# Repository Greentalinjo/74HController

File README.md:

# 74HC-ontroller

**A game controller built entirely from discrete 74HC logic.** Eight keys, a
diode ROM for a character table, and a real 8-N-1 serial frame out of an RJ45
console port — no microcontroller, no FPGA, no firmware, nothing programmable
anywhere on the board.

## Preface

This project started as an idea for a novel, old-school game controller to
plug into a MikroTik RB4011 that I own and am turning into a gaming console.
The RB4011 already has what a console needs to hear a controller — a serial
console port on an RJ45 jack — so the controller only has to do one thing:
turn a button press into a character on that line.

The twist is *how*. Instead of a microcontroller running a few lines of code,
every step — watching the buttons, noticing a change, looking up the
character, and shifting it out bit by bit at 115200 baud — is done by
sixteen logic chips from the 74HC family, the kind you would find in a 1980s
computer, plus one RS-232 line driver. Change the character a button sends by
moving a diode.

| At a glance | |
|---|---|
| Keys | 5-way navigation cluster + 3 Cherry MX switches |
| Output | 8-N-1 serial, 115200 baud by default, as RS-232 on an RJ45 (Cisco console pinout) or 3.3 V TTL on a header |
| Logic | 16 × 74HC-series ICs + a MAX3232 RS-232 transceiver |
| Key map | an 8 × 7 diode ROM — 56 positions, a diode wherever a bit is 1 |
| Power | one AA cell, boosted to 3.3 V; ~1.3 mA, roughly four weeks of continuous use |
| Board | 150 × 60 mm, 6 layers, 1.6 mm |
| Case | 3D-printed, three colours, sliding battery door |

---

## Contents

1. [How it works — the big picture](#1-how-it-works--the-big-picture)
2. [The pipeline, stage by stage](#2-the-pipeline-stage-by-stage)
3. [Putting it together: the life of a key press](#3-putting-it-together-the-life-of-a-key-press)
4. [What you can configure](#4-what-you-can-configure)
5. [Using it with a MikroTik console](#5-using-it-with-a-mikrotik-console)
6. [The hardware](#6-the-hardware)
7. [The case](#7-the-case)
8. [Building one](#8-building-one)
9. [Repository layout](#9-repository-layout)

---

## 1. How it works — the big picture

A microcontroller would handle a key press with a loop and an interrupt. This
board does the same job as a small **pipeline of hardware stages**, each on
its own schematic sheet, each handing a signal to the next:

```mermaid
flowchart LR
    subgraph clock["Power, clock, reset"]
        P["AA cell → boost → 3.3 V"]
        C["crystal → 74HC4060 → baud tap<br/>CLK / nCLK"]
        R["power-on reset<br/>POR_n"]
    end

    K["8 keys<br/>RC + Schmitt debounce"] --> L["74HC151<br/>LIVE key"]
    S["74HC161<br/>scan counter"] -- "address" --> L
    S -- "address" --> M["74HC259<br/>state memory"]
    M --> T["74HC151<br/>STORED key"]
    S -- "address" --> T
    L --> X["74HC86<br/>DIFF = LIVE xor STORED"]
    T --> X
    X --> B["74HC74<br/>BUSY"]
    B -- "freeze" --> S
    B --> Q["74HC161 + 74HC138<br/>frame sequencer"]
    Q -- "state 10: store" --> M
    S -- "address" --> D["74HC238 + diode ROM<br/>the character"]
    D --> SR["2 × 74HC165<br/>shift register"]
    SR --> G["74HC32<br/>output gate"]
    G --> O["JP4: TTL header<br/>or MAX3232 → RJ45"]
```

The idea in one paragraph: a counter **scans** the eight keys one at a time,
comparing each key's **live** state with the state the board **remembers**.
When they differ, a key has changed. The board then **freezes the scan** on
that key, uses the key's number to select a row of the **diode ROM** — which
presents that key's character — **shifts** the character out as a serial
frame, **stores** the key's new state so the difference disappears, and
**resumes** scanning. Everything is clocked by the baud-rate clock, so the
whole machine runs in lock-step with the serial line.

---

## 2. The pipeline, stage by stage

The schematic is split into seven sheets, in the order a signal travels
through them. A PDF of the whole schematic is in
[`docs/schematic.pdf`](docs/schematic.pdf).

### Stage 1 — Power, clock and reset *(sheet: Power, Clock, Reset)*

Everything else depends on three things from this sheet.

**Power.** One AA cell goes through the power switch (SW10) into an
**ME2108A33 boost converter** (U18, with L1, D3 and C1), which makes the
board's single **3.3 V** rail. It starts from a 0.9 V cell and keeps
regulating down to 0.45 V, so the battery is used to the end. JP1 can instead
take power from the TTL header. D1 is the power LED.

**Clock.** A **3.6864 MHz crystal** drives the oscillator inside a
**74HC4060** (U1), which also divides the frequency by powers of two. Jumper
**JP2** picks one of those outputs as the bit clock, `CLK` — by default
3.6864 MHz ÷ 32 = exactly **115200 Hz**, one tick per serial bit. A Schmitt
inverter makes `nCLK`, its opposite edge, which the control logic uses.

**Reset.** An RC network (R6, C5) and two Schmitt inverters hold `POR_n` low
for about 87 ms at switch-on, which clears the state memory, the scanner and
the BUSY flag — so the controller never sends a burst of junk characters when
it powers up. SW9 is a manual reset button.

### Stage 2 — Keys and debounce *(sheet: Keys and Debounce)*

Each of the eight keys has its own complete **debounce cell**: a 10 kΩ
pull-up, a 1 kΩ series resistor, a 1 µF capacitor to ground and a **74HC14
Schmitt-trigger** inverter.

```
+3V3 ──[10k]──┬──[1k]── switch ── GND
              │
             1µF          ──► 74HC14 ──► KEYn  (high while pressed)
              │
             GND
```

The cell is deliberately **asymmetric**: pressing discharges the capacitor
through 1 kΩ (a ~1.7 ms response), releasing recharges it through 10 kΩ
(~7.4 ms). The slow edges swallow contact bounce, and the Schmitt trigger
turns the slow analogue ramp into one clean logic edge.

The keys are **KEY0–KEY4**: the five directions of an SJMS 5-way navigation
cluster (SW1, one package) — **KEY5–KEY7**: three Cherry MX switches (SW6–SW8).

### Stage 3 — Scanner and memory *(sheet: Scanner and Memory)*

This stage decides *whether* anything needs sending.

* A **74HC161 counter** (U4) steps a 3-bit address, `ADDR0–2`, through the
  eight keys, one key per clock tick. A full sweep takes eight bit times.
* A **74HC151 multiplexer** (U5) reads the addressed key's live state: `LIVE`.
* A **74HC259 addressable latch** (U6) is the board's memory — eight bits
  holding the last state that was *reported* for each key.
* A second **74HC151** (U7) reads the remembered state of the same key:
  `STORED`. (The '259 has no read-back port of its own, so this second
  multiplexer is essential.)
* A **74HC86 XOR** gate compares the two: `DIFF = LIVE xor STORED`.

`DIFF` goes high exactly when the key under the scanner has changed since it
was last reported. That is the only event this whole machine reacts to.

### Stage 4 — Transmit sequencer *(sheet: Transmit Sequencer)*

This stage runs a transmission once `DIFF` says there is something to send.

* **`BUSY`** — a 74HC74 flip-flop (U9A) captures `DIFF` on the `nCLK` edge.
  While `BUSY` is high, the scan counter is **frozen** through its count
  enables. The clock itself is never gated, so there are no glitches.
* A second **74HC161** (U10) counts the bit times of the frame, and a
  **74HC138** decoder (U11) picks out two moments from that count:
  * **State 10** — the frame has finished, so it pulses the 74HC259's write
    enable. The key's new state is stored, `DIFF` falls, and on the next edge
    `BUSY` clears itself and the scanner moves on.
  * **State 11** — a lock-up escape. If `DIFF` somehow failed to clear, the
    second flip-flop (U9B) forces `BUSY` off, so the controller can never
    freeze for good.

The whole event takes **11 bit times**: 10 for the frame, 1 to store and
resume. That's about 95 µs at 115200 baud.

### Stage 5 — ASCII diode ROM *(sheet: ASCII Diode ROM)*

This stage decides *what* gets sent. It is a real read-only memory, built
from diodes:

* A **74HC238 decoder** (U14) takes the frozen key address and drives exactly
  one of eight **rows** high — one row per key.
* Seven **columns** run across the rows, one per bit of the ASCII code
  (b0–b6), each held low by a 15 kΩ pull-down (R30–R36).
* Where a bit should be 1, a **diode** connects that key's row to that bit's
  column (anode to the row, cathode to the column). Driving the row pulls
  those columns high; the rest stay low.

Of the 56 positions (8 keys × 7 bits), **27 are fitted** for the default key
map. The decoder is only enabled while `DIFF` is high, so the ROM draws
nothing at rest.

### Stage 6 — UART shift register *(sheet: UART Shift Register)*

Two **74HC165 shift registers** (U15, U16) are chained into a 16-bit
register that holds the whole frame:

| Frame bit | Comes from |
|---|---|
| start (0) | tied to ground |
| b0 … b6 | the ROM columns |
| bit 7 | make/break flag (see §4) |
| stop (1) | tied to 3.3 V |
| idle (1s) | tied to 3.3 V |

While the board is idle, `BUSY` holds the registers in **parallel load**, so
the start bit is already waiting on the output. The instant `BUSY` rises they
start shifting — one bit per `nCLK` — which produces the serial frame
directly, least-significant bit first.

A **74HC32 OR gate** (U13) then forms the final line:
`TX = shift register OR not-BUSY OR SUPPRESS`. `not-BUSY` parks the line high
(idle) between frames, and `SUPPRESS` blanks a key-*release* frame when break
codes are turned off.

### Stage 7 — Output *(sheet: Output Stage)*

The finished 3.3 V serial line goes to **JP4**, which sends it one of two ways:

* **RS-232** — through a **MAX3232** (U17) to the **RJ45** console jack, using
  the Cisco console pinout that MikroTik and most network gear use.
* **3.3 V TTL** — to the 4-pin header **J3**, for a USB-serial adapter or
  another board.

The MAX3232's spare receiver also converts the *other* direction: whatever
the connected device prints on its console comes back as 3.3 V TTL on J3 pin
3, so you can watch the console while the controller drives it.

---

## 3. Putting it together: the life of a key press

Everything is timed in **bit times** (one `CLK` period: 8.7 µs at 115200
baud). The control logic acts on `nCLK`, half a bit away from the scanner's
`CLK`, so the scan address is always settled before anything reads it.

| When | What happens |
|---|---|
| — | You press a key. The debounce cell settles, and `KEYn` goes high about 1.7 ms later. |
| within 8 bit times | The scanner reaches that key. `LIVE` = 1, `STORED` = 0, so **`DIFF` = 1**. |
| f0 | `BUSY` rises on `nCLK`. The scanner **freezes**, the ROM row for this key is driven, and the shift registers start sending — the **start bit** is already on the line. |
| f1 – f7 | ASCII bits **b0 … b6**, straight from the diode ROM. |
| f8 | **bit 7** (0 unless make/break codes are on). |
| f9 | **stop bit**. |
| f10 | Sequencer state 10: the new key state is **written into memory**. `DIFF` falls. |
| f11 | `BUSY` clears itself. The scanner **resumes**. |

Releasing the key is the same event in reverse: the key now differs from
memory again, so another frame is sent, or quietly suppressed if break codes
are off.

Because each change is handled on its own sweep, pressing all eight keys at
once produces eight clean frames back to back (8.8 ms at 9600 baud, under
1 ms at 115200). Nothing is lost and nothing is merged, since only one key
can be transmitting at a time.

---

## 4. What you can configure

Everything is set with jumpers, solder bridges and diodes. There's no
firmware to reflash.

### Jumpers at a glance

| Ref | What it sets | Options | Default |
|---|---|---|---|
| **JP1** | Power source | 1-2 AA cell via the boost converter · 2-3 from TTL header J3 pin 4 | 1-2 |
| **JP2** | Baud rate | one shunt across one of seven columns (below) | column 2 = 115200 |
| **JP3** | Break codes | open = press only · fitted = press *and* release | open |
| **JP4** | Output | 1-2 RS-232 on the RJ45 · 2-3 3.3 V TTL on J3 | 2-3 |
| **JP5** | Both outputs | solder bridge: drive RS-232 *and* TTL at once | open |
| **JP6 / JP7** | RJ45 cable type | both 2-3 straight patch cable · both 1-2 rollover console cable | 2-3 |
| **JP8 / JP9** | Handshake | solder bridges that assert DSR / CTS, for devices that insist | open |

### Baud rate — JP2 and the crystal

JP2 picks a divider tap from the 74HC4060. Its seven columns follow the
chip's pin order, **not** baud order. That keeps the wiring uncrossed, and a
table on sheet 2 of the schematic maps them.

| JP2 column | 1 | 2 | 3 | 4 | 5 | 6 | 7 |
|---|---|---|---|---|---|---|---|
| '4060 tap | Q6 ÷64 | Q5 ÷32 | Q7 ÷128 | Q4 ÷16 | Q10 ÷1024 | Q8 ÷256 | Q9 ÷512 |
| **3.6864 MHz** (fitted) | 57600 | **115200** | 28800 | 230400 | 3600 | 14400 | 7200 |
| 4.9152 MHz | 76800 | 153600 | 38400 | 307200 | 4800 | 19200 | **9600** |

115200 and 9600 differ by a factor of 12, not a power of two, so no single
crystal reaches both. For a 9600-baud controller, fit a 4.9152 MHz crystal
and use column 7.

### The key map — moving diodes

Each key sends the 7-bit ASCII code wired into its row of the ROM. The diode
for **key *k*, bit *b*** is **D2*kb***. For example, D245 is key 4, bit 5.
Fit a diode wherever the bit should be 1.

| Key | Button | Sends | Code | Diodes fitted |
|---|---|---|---|---|
| 0 | nav centre / OK | Enter (CR) | 0x0D | D200 D202 D203 |
| 1 | nav up | Tab | 0x09 | D210 D213 |
| 2 | nav down | Esc | 0x1B | D220 D221 D223 D224 |
| 3 | nav left | Ctrl-C | 0x03 | D230 D231 |
| 4 | nav right | `/` | 0x2F | D240 D241 D242 D243 D245 |
| 5 | MX 1 | `?` | 0x3F | D250 D251 D252 D253 D254 D255 |
| 6 | MX 2 | Space | 0x20 | D265 |
| 7 | MX 3 | `q` | 0x71 | D270 D274 D275 D276 |

The silkscreen labels the grid like a table, since 56 designators would not
fit. Across the top is `D20 21 22 … 27`, one label per key column. Down the
right side is `0`–`6`, one per bit, next to that bit's pull-down R30–R36. A
diode's designator is the label above it followed by the digit beside it.

### Press-only or make/break — JP3

* **Open (default):** a key sends its character when pressed and nothing on
  release. This is plain typing, the right choice for a console.
* **Fitted:** a press sends `0x80 | code` and a release sends `code`. Bit 7
  carries the key's state, which gives a game true key-down/key-up events.

### Output — JP4, JP5, JP6/JP7, JP8/JP9

* **JP4** chooses RS-232 on the RJ45 or 3.3 V TTL on J3. The unused output is
  held at its idle level, not left floating.
* **JP5** drives both outputs at once.
* **JP6/JP7** move the transmit and receive lines between RJ45 pins 3 and 6,
  so both a straight patch cable and a rollover console cable work. Always
  move them together.
* **JP8/JP9** assert DSR and CTS from a spare driver. RouterOS doesn't need
  them.

**J3 (TTL header):** 1 GND · 2 TXD out · 3 RXD (the far end's console, as
3.3 V TTL) · 4 +3.3 V, in or out depending on JP1.

### Other options

* **Power LED:** leave D1 and R3 off to save 0.28 mA, about a quarter of the
  idle current.
* **R53** stays unfitted. It belonged to a 5 V version of the design and
  would now pull the TTL output below a 3.3 V input's threshold.

---

## 5. Using it with a MikroTik console

1. Set **JP4 to 1-2** (RS-232), and leave JP6/JP7 on 2-3.
2. Connect the controller's RJ45 to the router's **Serial** console port with
   an ordinary straight Ethernet patch cable.
3. The console runs at **115200 8-N-1**, which is JP2's default. RouterBOOT's
   console rate can't be changed, which is why the controller runs at
   115200 rather than 9600.
4. Switch on. Every key press arrives on the console as a plain keystroke,
   ready for whatever is reading it.

For a PC instead, set JP4 to 2-3 and plug a 3.3 V USB-serial adapter into
J3.

---

## 6. The hardware

* **150 × 60 mm, 6-layer, 1.6 mm.** Signals run on the outer layers. Ground
  is poured on the top, bottom and three inner layers, and the 3.3 V supply
  has its own inner plane.
* **Front:** the navigation cluster, the three MX switches, the diode ROM and
  its decoder and pull-downs, one of the shift registers and some decoupling.
* **Back:** the rest of the logic, the RJ45, the TTL and jumper headers, the
  power switch, the reset button and the AA holder.
* **Parts:** all logic in SOIC. Passives are 0603/0402, with 0805 for the 1 µF
  debounce capacitors, and the ROM diodes are SOD-523. Through-hole parts are
  used only where needed: switches, connectors, headers, the AA holder, C1
  and D3.
* **Four M3 mounting holes** (H1–H4) take the case screws.

Three parts have requirements the footprint alone doesn't capture:

* **C30–C37 and C5 (1 µF) must be 0805 X7R.** A 1 µF 0402 part loses so much
  capacitance under DC bias that the debounce timing guarantee breaks at
  9600 baud.
* **C3/C4 (30 pF crystal load) must be C0G/NP0**, to keep the oscillator
  stable and starting reliably.
* **U17 must be a MAX3232** (or MAX232A/SP3232), not a plain MAX232, which
  needs 1 µF pump capacitors. The logic must be **74HC**, not 74HCT or 74LS.

### How it was checked

Before any copper was ordered, the design's netlist was run in a purpose-built
logic simulator that models every IC against its datasheet truth table.
Switches were driven through the real RC debounce values, and the serial
output was decoded like a real UART receiver. The runs covered:
* 108 scenarios, including every key, eight keys at once, bounce, make/break,
  both outputs and a deliberate lock-up;
* 1,268 randomised and exhaustive assertions, including all 255 key
  combinations;
* a DC noise-margin check of every logic level at 3.3 V.

The simulator isn't part of this repository. The schematic passes KiCad ERC
with no errors, and the board passes DRC and matches the schematic.

---

## 7. The case

A three-piece 3D-printed enclosure, ready to slice, in [`case/`](case/):

| File | Part | Print |
|---|---|---|
| `top_with_trim.3mf` | top shell, holding the switches | three colours: plate, trim and logo inlays. Print plate side down, no supports |
| `bottom.3mf` | bottom shell | print on its raised hump. Support only the flat undersides (grid supports, build plate only, 2–3 interface layers, a brim) |
| `door.3mf` | battery door | outer face down, no supports |

The case is shaped to be held in both hands from the ends. The bottom steps
down only where the tall parts are (the battery, power switch and RJ45) and
slopes up everywhere else. It has:
* windows over every jumper header;
* a pinhole for the reset button;
* a pocket for the power switch lever;
* a small light hole for the power LED;
* an RJ45 opening in the top wall.

**Hardware:** five **M3 × 8 pan-head screws** and five **M3 heat-set
inserts**, which go in 4.2 mm holes up to 8 mm deep.

**Assembly:**
1. Clip the switches into the top plate and solder the PCB to them.
2. Press heat-set inserts into the tops of the bottom shell's four posts, and
   the fifth into the battery door's screw boss, from underneath.
3. Close the bottom and drive four screws down through the counterbored holes
   in the top, so the heads sit flush, through the PCB and into the inserts.
4. Drop the battery door into its seat, slide it right so its tongues go
   under the lip, and fix it with the fifth screw.

---

## 8. Building one

1. **The PCB.** Open `kicad/logic-macropad.kicad_pro` in **KiCad 10** or newer
   and plot gerbers and drill files. The project is self-contained, with its
   own symbol and footprint libraries. Order 6 layers, 1.6 mm, FR-4. Nothing
   on the board is impedance-sensitive, so any standard stackup works.
2. **The parts.** Every symbol carries its specification and an example part
   number in its fields. *Tools → Generate BOM* in the schematic editor, or
   `kicad-cli sch export bom`, lists them. The 29 unused ROM positions and
   R53 are marked *do not populate*.
3. **Assembly.** Everything is hand-solderable, but the SOD-523 ROM diodes are
   small. Fit only the diodes for your key map (§4). Set the jumpers, fit an
   AA cell, and switch on.

---

## 9. Repository layout

```
kicad/                          the KiCad 10 project
  logic-macropad.kicad_pro        project, design rules
  logic-macropad.kicad_sch        root sheet: block diagram, the seven stages
  01_power_clock.kicad_sch        stage 1  power, clock, reset
  02_keys_debounce.kicad_sch      stage 2  keys and debounce
  03_scanner.kicad_sch            stage 3  scanner and memory
  04_sequencer.kicad_sch          stage 4  transmit sequencer
  05_ascii_rom.kicad_sch          stage 5  ASCII diode ROM
  06_uart_tx.kicad_sch            stage 6  UART shift register
  07_output.kicad_sch             stage 7  output stage
  logic-macropad.kicad_pcb        the 6-layer board
  lib/, logic-macropad.pretty/    project symbols and footprints
case/                           print-ready 3MF files for the enclosure
docs/
  schematic.pdf                   the full schematic
  images/                         renders used in this README
```

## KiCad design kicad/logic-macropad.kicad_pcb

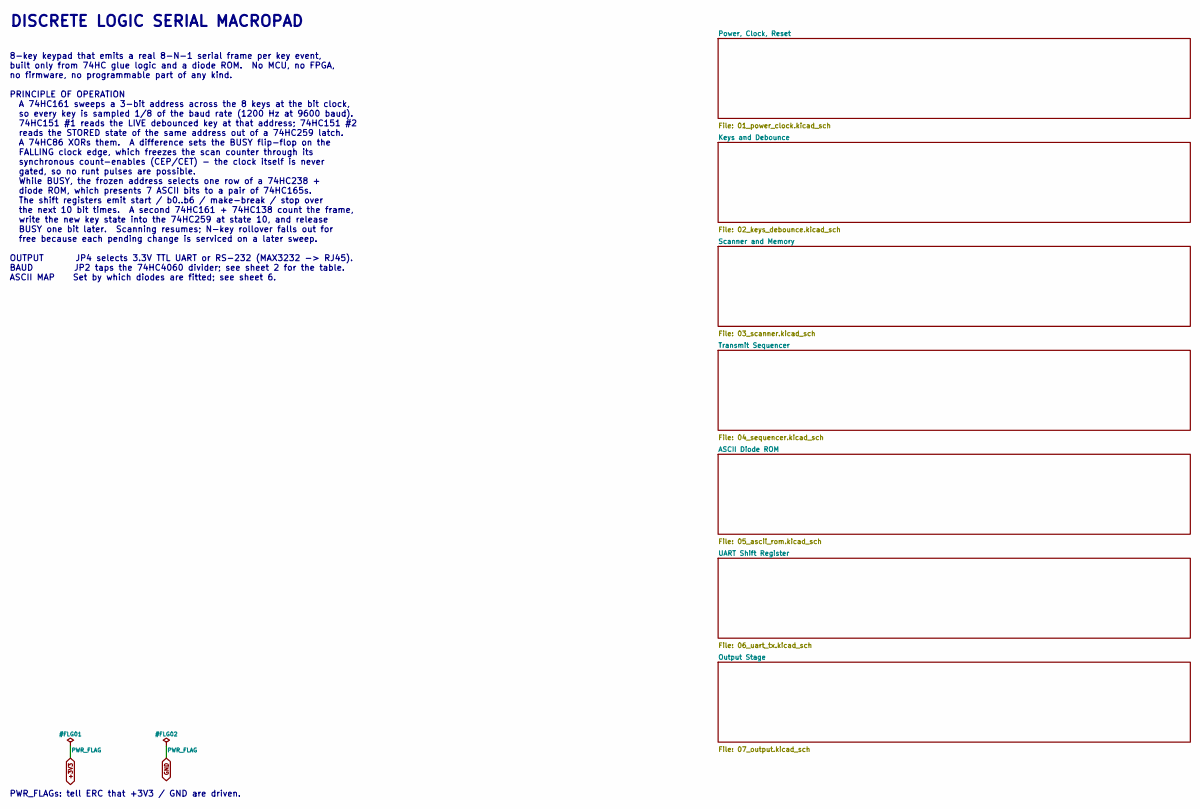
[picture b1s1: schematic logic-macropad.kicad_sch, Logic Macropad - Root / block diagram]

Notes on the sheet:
8-key keypad that emits a real 8-N-1 serial frame per key event, built only from 74HC glue logic and a diode ROM. No MCU, no FPGA, no firmware, no programmable part of any kind. PRINCIPLE OF OPERATION A 74HC161 sweeps a 3-bit address across the 8 keys at the bit clock, so every key is sampled 1/8 o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
PWR_FLAGs: tell ERC that +3V3 / GND are driven.
DISCRETE LOGIC SERIAL MACROPAD

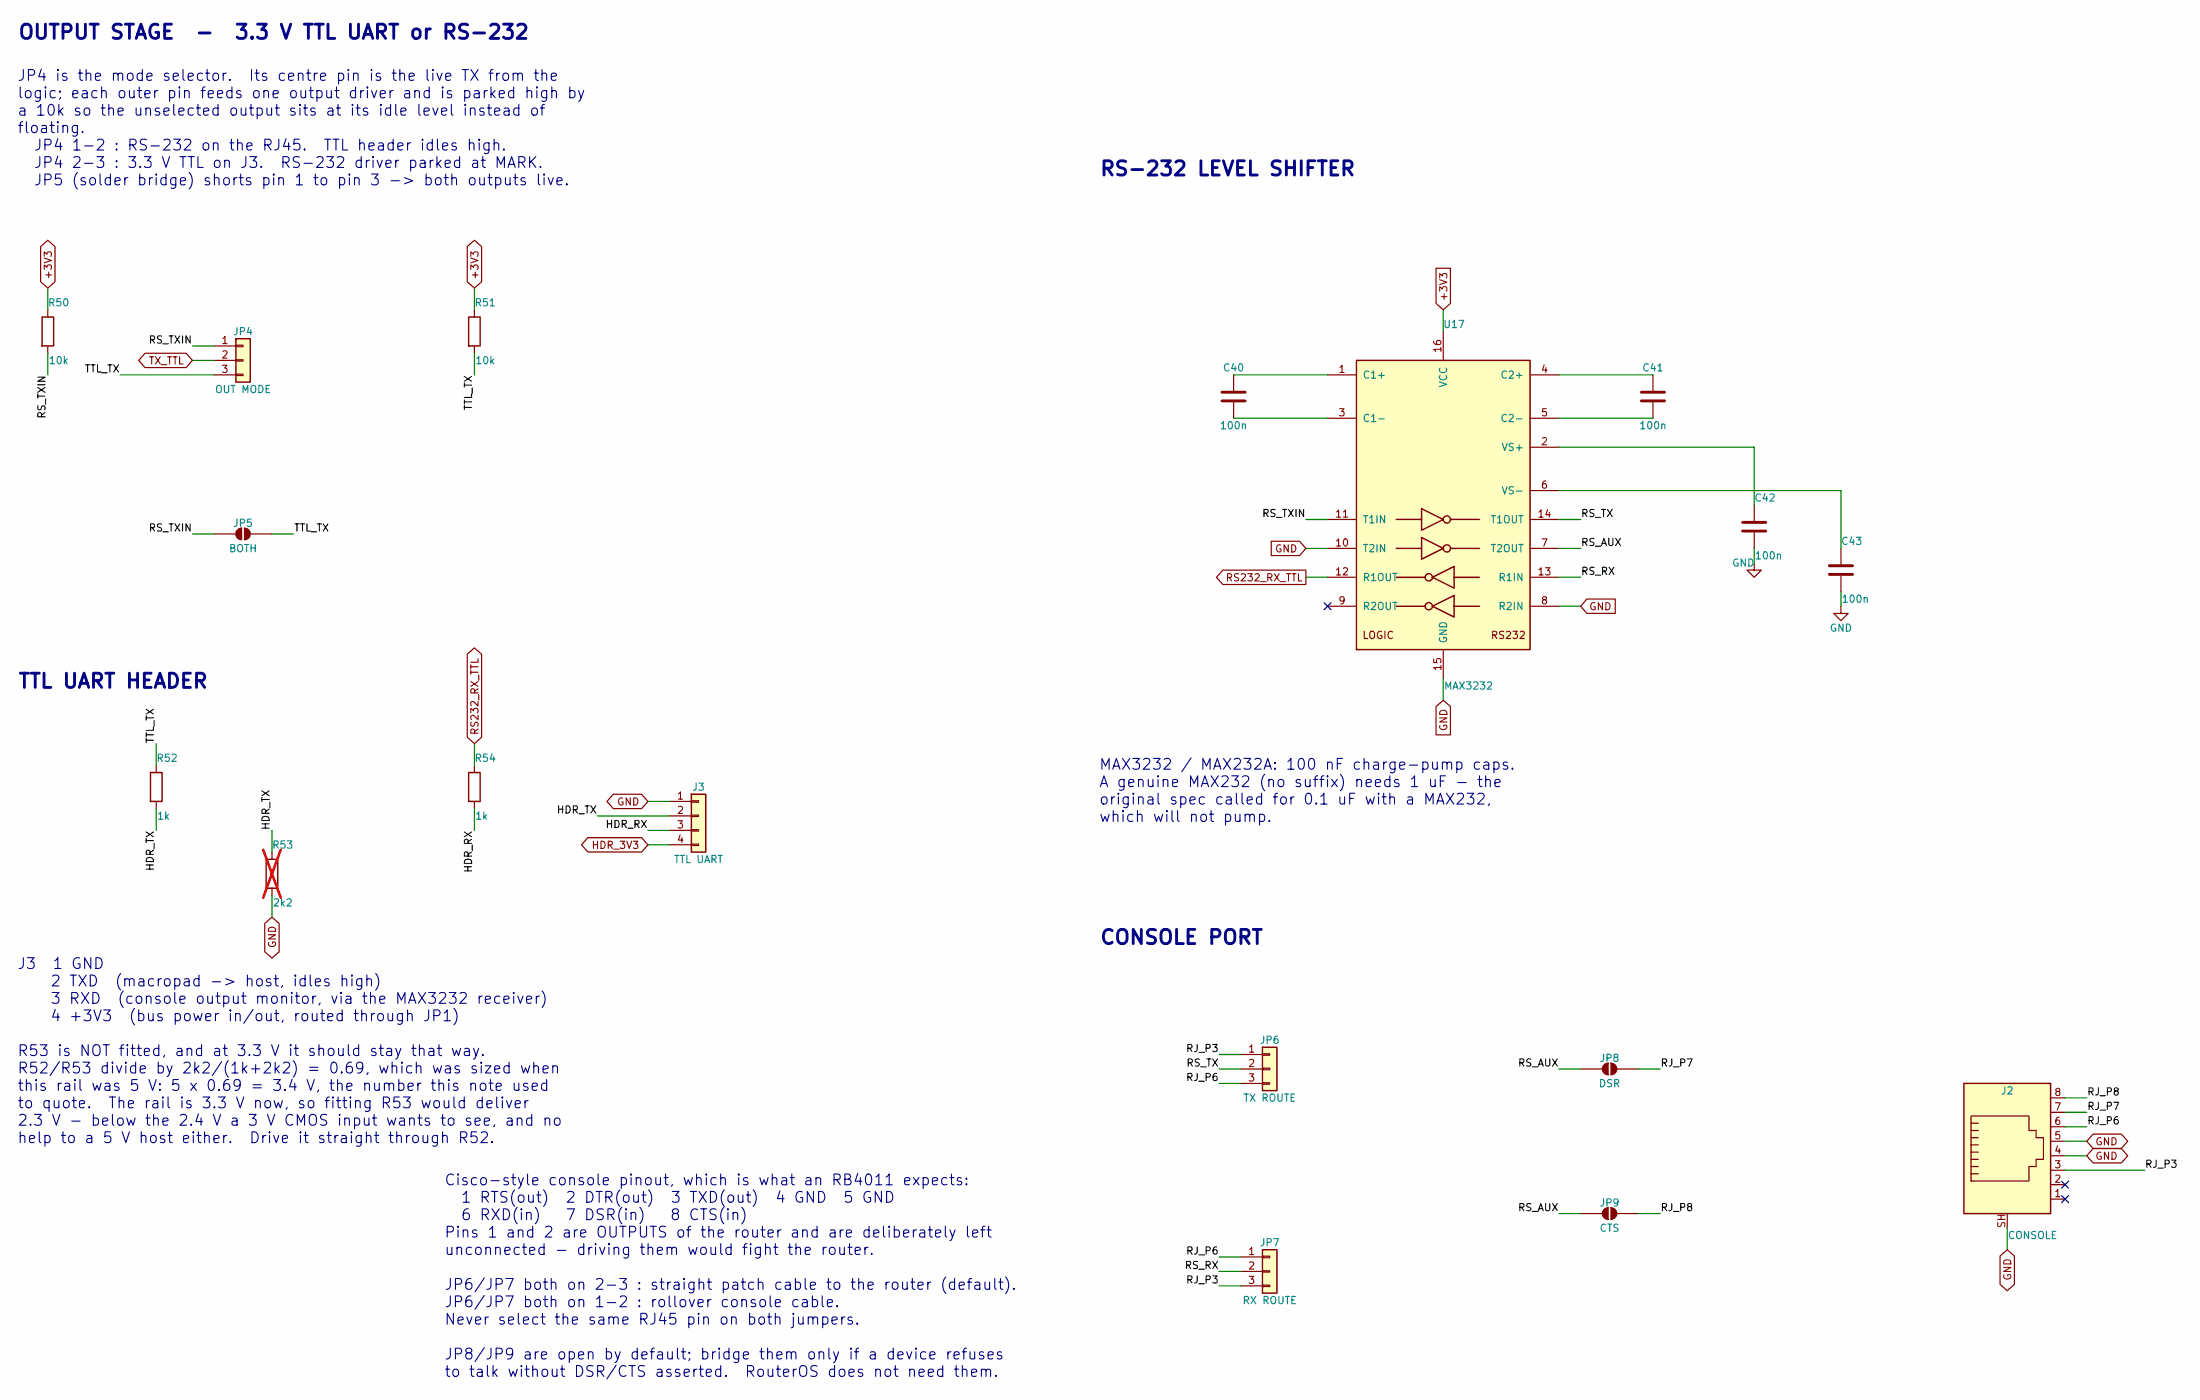
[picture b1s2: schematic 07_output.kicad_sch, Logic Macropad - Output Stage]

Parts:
C40, C41, C42, C43: 100n; C_0402_1005Metric; MPN GRM155R71H104KE14D
J2: CONSOLE; RJ45_8P8C_Shielded_HCTL_HC-RJ45-5JA-1-4; MPN HC-RJ45-5JA-1-4
J3: TTL UART; PinHeader_1x04_P2.54mm_Vertical; MPN 2.54-1*40P
JP4: OUT MODE; PinHeader_1x03_P2.54mm_Vertical; MPN 2.54-1*40P
JP5: BOTH; SolderJumper-2_P1.3mm_Open_RoundedPad1.0x1.5mm
JP6: TX ROUTE; PinHeader_1x03_P2.54mm_Vertical; MPN 2.54-1*40P
JP7: RX ROUTE; PinHeader_1x03_P2.54mm_Vertical; MPN 2.54-1*40P
JP8: DSR; SolderJumper-2_P1.3mm_Open_RoundedPad1.0x1.5mm
JP9: CTS; SolderJumper-2_P1.3mm_Open_RoundedPad1.0x1.5mm
R50, R51: 10k; R_0603_1608Metric
R52, R54: 1k; R_0603_1608Metric
R53: 2k2; R_0603_1608Metric; not fitted
U17: MAX3232; SOIC-16_3.9x9.9mm_P1.27mm; MPN MAX3232CSE+

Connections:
+3V3: R50.1, R51.1, U17.16 (VCC); also elsewhere on the board
/Output Stage/HDR_RX: J3.3, R54.2
/Output Stage/HDR_TX: J3.2, R52.2, R53.1
/Output Stage/RJ_P3: J2.3, JP6.1, JP7.3
/Output Stage/RJ_P6: J2.6, JP6.3, JP7.1
/Output Stage/RJ_P7: J2.7, JP8.2 (B)
/Output Stage/RJ_P8: J2.8, JP9.2 (B)
/Output Stage/RS_AUX: JP8.1 (A), JP9.1 (A), U17.7 (T2OUT)
/Output Stage/RS_RX: JP7.2, U17.13 (R1IN)
/Output Stage/RS_TX: JP6.2, U17.14 (T1OUT)
/Output Stage/RS_TXIN: JP4.1, JP5.1 (A), R50.2, U17.11 (T1IN)
/Output Stage/TTL_TX: JP4.3, JP5.2 (B), R51.2, R52.1
GND: C42.2, C43.2, J2.4, J2.5, J2.SH, J3.1, R53.2, U17.8 (R2IN), U17.10 (T2IN), U17.15 (GND); also elsewhere on the board
HDR_3V3: J3.4; also elsewhere on the board
unnamed: C40.1, U17.1 (C1+)
unnamed: C40.2, U17.3 (C1-)
unnamed: C41.1, U17.4 (C2+)
unnamed: C41.2, U17.5 (C2-)
unnamed: C42.1, U17.2 (VS+)
unnamed: C43.1, U17.6 (VS-)
RS232_RX_TTL: R54.1, U17.12 (R1OUT)
TX_TTL: JP4.2; also elsewhere on the board

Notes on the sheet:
OUTPUT STAGE - 3.3 V TTL UART or RS-232
Cisco-style console pinout, which is what an RB4011 expects: 1 RTS(out) 2 DTR(out) 3 TXD(out) 4 GND 5 GND 6 RXD(in) 7 DSR(in) 8 CTS(in) Pins 1 and 2 are OUTPUTS of the router and are deliberately left unconnected - driving them would fight the router. JP6/JP7 both on 2-3 : straight patch cable to t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
J3 1 GND 2 TXD (macropad -> host, idles high) 3 RXD (console output monitor, via the MAX3232 receiver) 4 +3V3 (bus power in/out, routed through JP1) R53 is NOT fitted, and at 3.3 V it should stay that way. R52/R53 divide by 2k2/(1k+2k2) = 0.69, which was sized when this rail was 5 V: 5 x 0.69 = 3.4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
JP4 is the mode selector. Its centre pin is the live TX from the logic; each outer pin feeds one output driver and is parked high by a 10k so the unselected output sits at its idle level instead of floating. JP4 1-2 : RS-232 on the RJ45. TTL header idles high. JP4 2-3 : 3.3 V TTL on J3. RS-232 driv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
RS-232 LEVEL SHIFTER
TTL UART HEADER
MAX3232 / MAX232A: 100 nF charge-pump caps. A genuine MAX232 (no suffix) needs 1 uF - the original spec called for 0.1 uF with a MAX232, which will not pump.
CONSOLE PORT

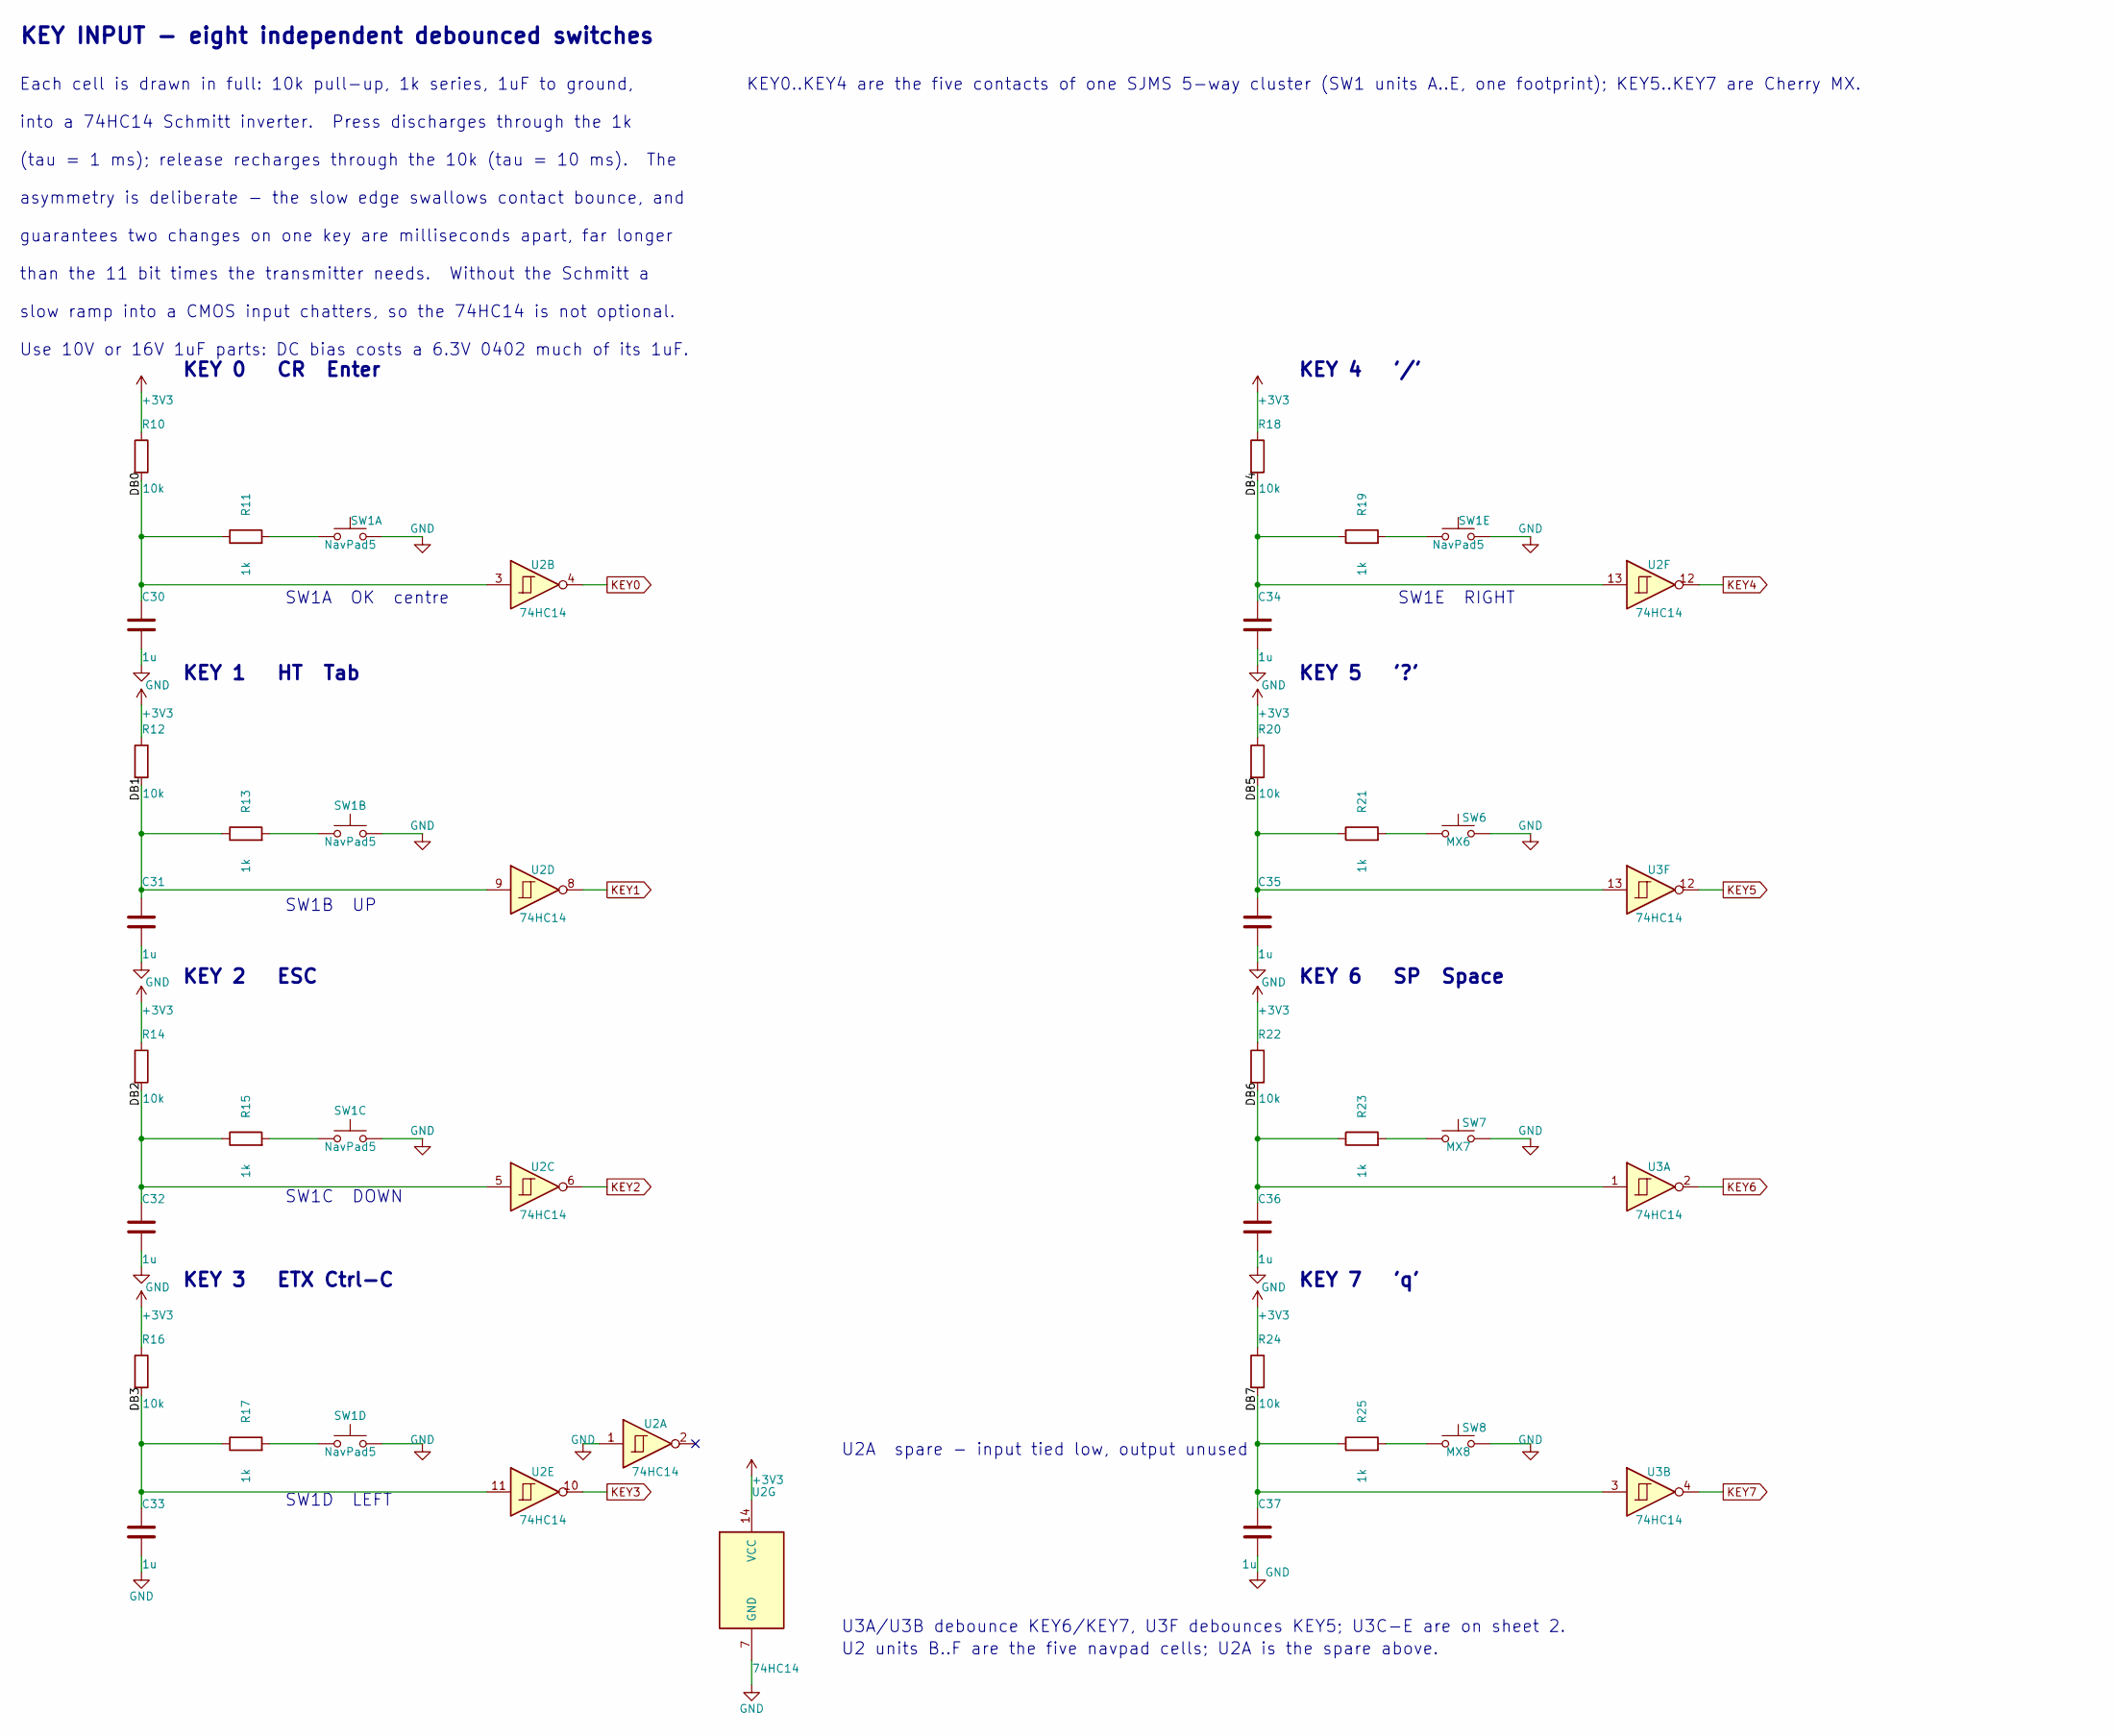
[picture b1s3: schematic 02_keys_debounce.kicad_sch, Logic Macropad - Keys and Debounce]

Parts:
C30, C31, C32, C33, C34, C35, C36, C37: 1u; C_0805_2012Metric; MPN GRM21BR71H105KA12L
R10, R12, R14, R16, R18, R20, R22, R24: 10k; R_0603_1608Metric
R11, R13, R15, R17, R19, R21, R23, R25: 1k; R_0603_1608Metric
SW1: NavPad5; SW_NavPad5_12x12_SJMS
SW6: MX6; SW_Cherry_MX_1.00u_PCB
SW7: MX7; SW_Cherry_MX_1.00u_PCB
SW8: MX8; SW_Cherry_MX_1.00u_PCB
U2, U3: 74HC14; SOIC-14_3.9x8.7mm_P1.27mm; MPN 74HC14D

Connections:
+3V3: R10.1, R12.1, R14.1, R16.1, R18.1, R20.1, R22.1, R24.1, U2.14 (VCC); also elsewhere on the board
/Keys and Debounce/DB0: C30.1, R10.2, R11.1, U2.3
/Keys and Debounce/DB1: C31.1, R12.2, R13.1, U2.9
/Keys and Debounce/DB2: C32.1, R14.2, R15.1, U2.5
/Keys and Debounce/DB3: C33.1, R16.2, R17.1, U2.11
/Keys and Debounce/DB4: C34.1, R18.2, R19.1, U2.13
/Keys and Debounce/DB5: C35.1, R20.2, R21.1, U3.13
/Keys and Debounce/DB6: C36.1, R22.2, R23.1, U3.1
/Keys and Debounce/DB7: C37.1, R24.2, R25.1, U3.3
GND: C30.2, C31.2, C32.2, C33.2, C34.2, C35.2, C36.2, C37.2, SW1.2, SW1.4 (2), SW1.6 (2), SW1.8 (2), SW1.10 (2), SW6.2, SW7.2, SW8.2, U2.1, U2.7 (GND); also elsewhere on the board
KEY0: U2.4; also elsewhere on the board
KEY1: U2.8; also elsewhere on the board
KEY2: U2.6; also elsewhere on the board
KEY3: U2.10; also elsewhere on the board
KEY4: U2.12; also elsewhere on the board
KEY5: U3.12; also elsewhere on the board
KEY6: U3.2; also elsewhere on the board
KEY7: U3.4; also elsewhere on the board
unnamed: R11.2, SW1.1
unnamed: R21.2, SW6.1
unnamed: R23.2, SW7.1
unnamed: R25.2, SW8.1
unnamed: R13.2, SW1.3 (1)
unnamed: R15.2, SW1.5 (1)
unnamed: R17.2, SW1.7 (1)
unnamed: R19.2, SW1.9 (1)

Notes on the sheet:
into a 74HC14 Schmitt inverter. Press discharges through the 1k
SW1E RIGHT
U3A/U3B debounce KEY6/KEY7, U3F debounces KEY5; U3C-E are on sheet 2.
KEY 1 HT Tab
asymmetry is deliberate - the slow edge swallows contact bounce, and
KEY 7 'q'
KEY0..KEY4 are the five contacts of one SJMS 5-way cluster (SW1 units A..E, one footprint); KEY5..KEY7 are Cherry MX.
SW1C DOWN
U2A spare - input tied low, output unused
U2 units B..F are the five navpad cells; U2A is the spare above.
KEY 4 '/'
Use 10V or 16V 1uF parts: DC bias costs a 6.3V 0402 much of its 1uF.
KEY 5 '?'
slow ramp into a CMOS input chatters, so the 74HC14 is not optional.
than the 11 bit times the transmitter needs. Without the Schmitt a
KEY 6 SP Space
(tau = 1 ms); release recharges through the 10k (tau = 10 ms). The
SW1B UP
SW1D LEFT
Each cell is drawn in full: 10k pull-up, 1k series, 1uF to ground,
KEY 0 CR Enter
KEY 2 ESC
KEY INPUT - eight independent debounced switches
SW1A OK centre
KEY 3 ETX Ctrl-C
guarantees two changes on one key are milliseconds apart, far longer

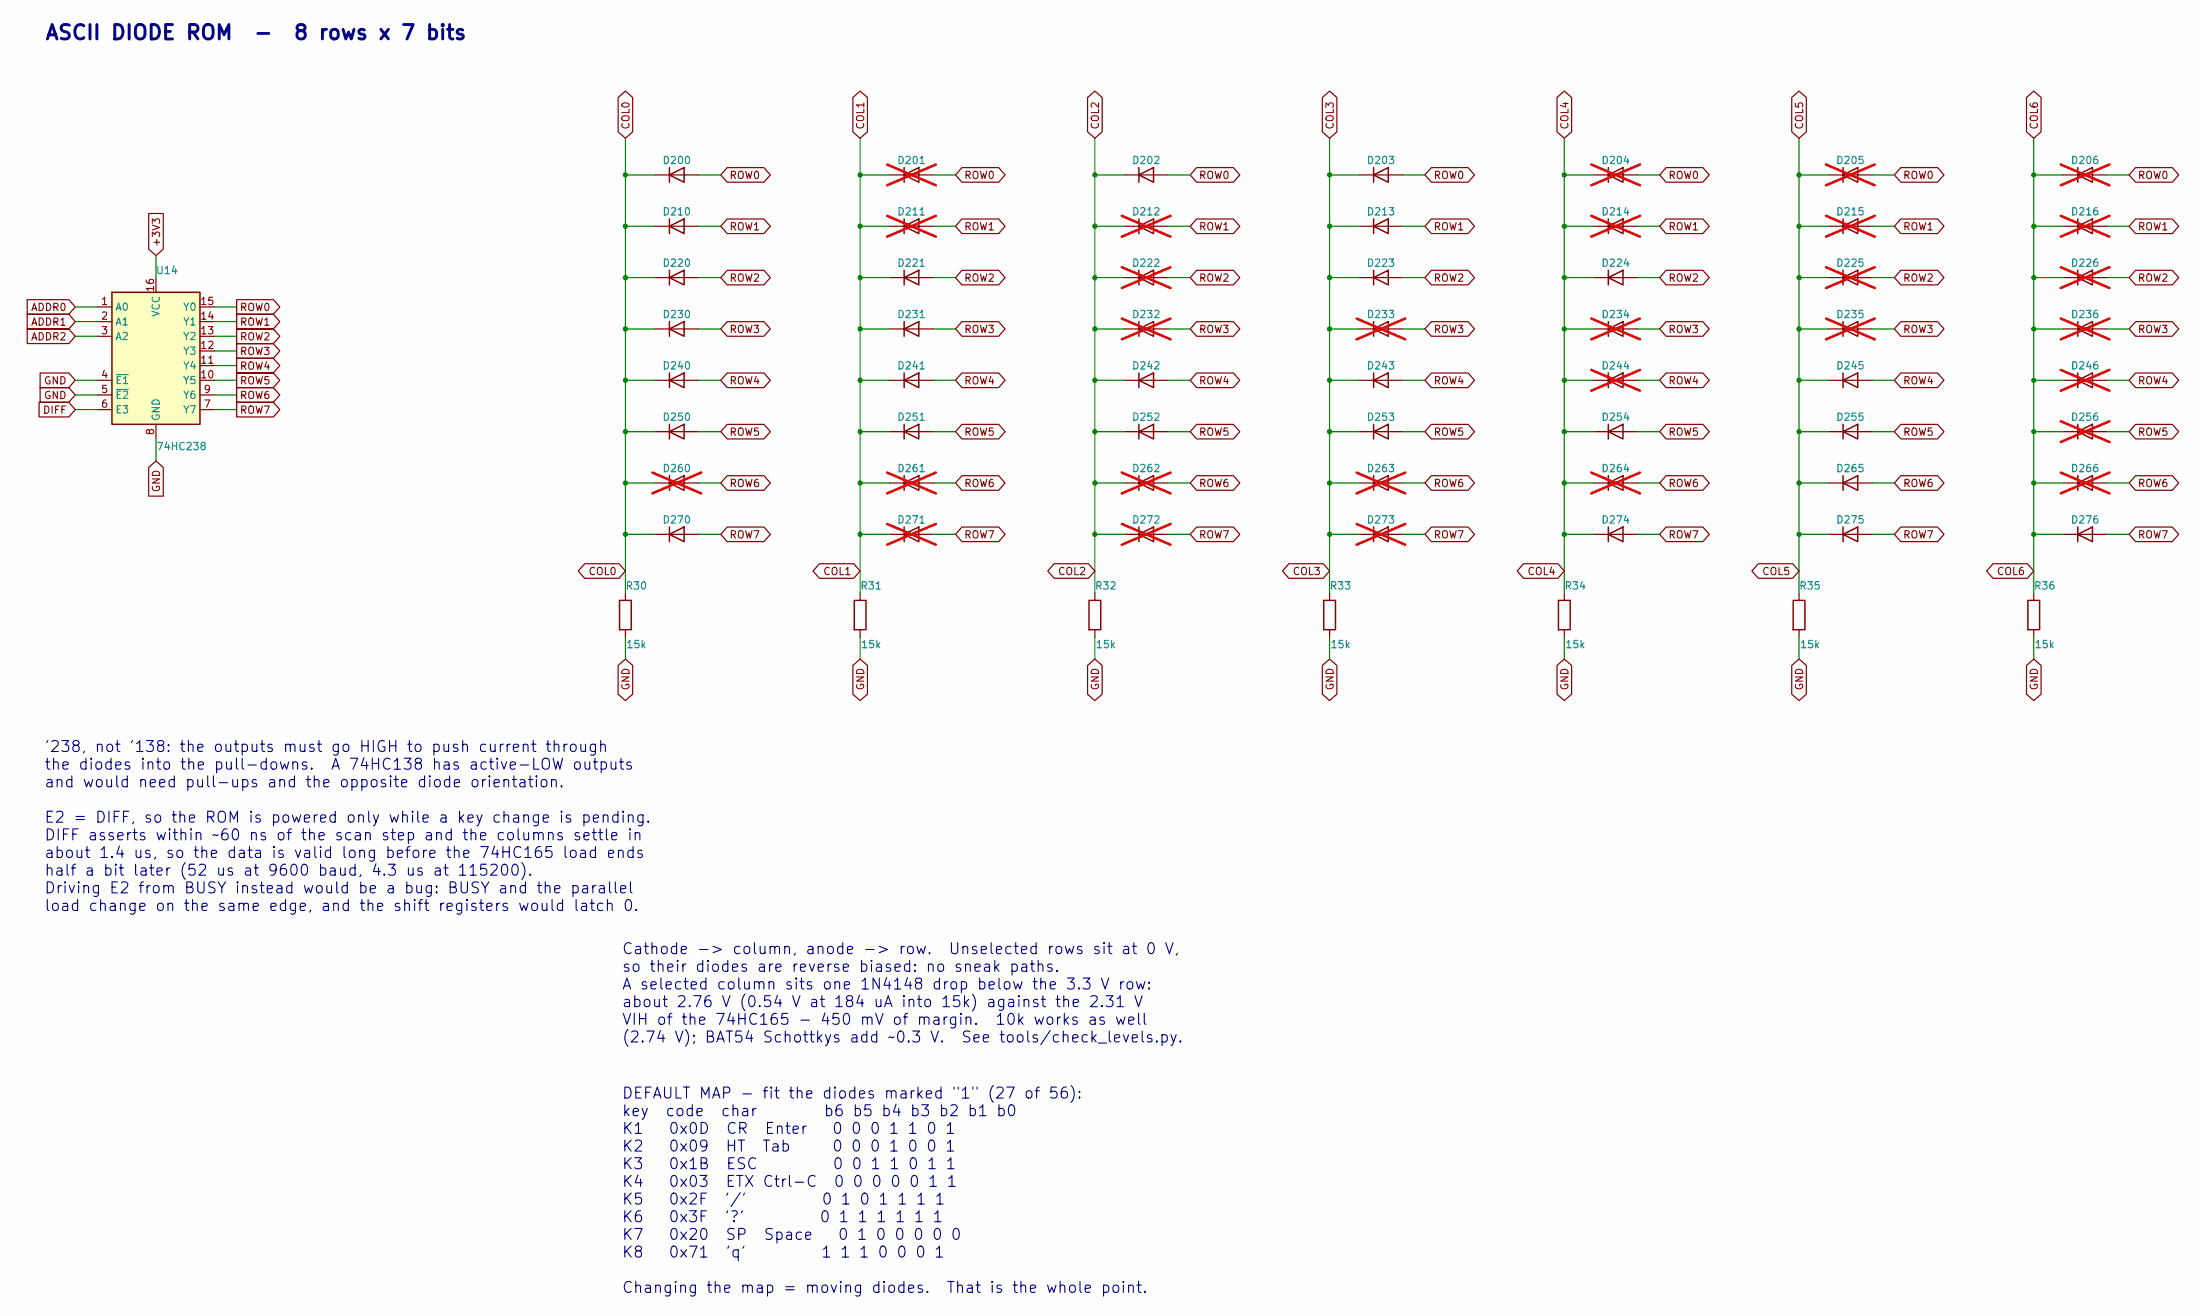
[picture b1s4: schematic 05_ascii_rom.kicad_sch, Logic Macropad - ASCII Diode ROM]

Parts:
D200, D202, D203, D210, D213, D220, D221, D223, D224, D230, D231, D240, D241, D242, D243, D245, D250, D251, D252, D253, D254, D255, D265, D270, D274, D275, D276: 1N4148; D_SOD-523; MPN 1N4148WT-7
D201, D204, D205, D206, D211, D212, D214, D215, D216, D222, D225, D226, D232, D233, D234, D235, D236, D244, D246, D256, D260, D261, D262, D263, D264, D266, D271, D272, D273: 1N4148; D_SOD-523; not fitted
R30, R31, R32, R33, R34, R35, R36: 15k; R_0603_1608Metric
U14: 74HC238; SOIC-16_3.9x9.9mm_P1.27mm; MPN 74HC238D

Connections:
+3V3: U14.16 (VCC); also elsewhere on the board
ADDR0: U14.1 (A0); also elsewhere on the board
ADDR1: U14.2 (A1); also elsewhere on the board
ADDR2: U14.3 (A2); also elsewhere on the board
COL0: D200.1 (K), D210.1 (K), D220.1 (K), D230.1 (K), D240.1 (K), D250.1 (K), D260.1 (K), D270.1 (K), R30.1; also elsewhere on the board
COL1: D201.1 (K), D211.1 (K), D221.1 (K), D231.1 (K), D241.1 (K), D251.1 (K), D261.1 (K), D271.1 (K), R31.1; also elsewhere on the board
COL2: D202.1 (K), D212.1 (K), D222.1 (K), D232.1 (K), D242.1 (K), D252.1 (K), D262.1 (K), D272.1 (K), R32.1; also elsewhere on the board
COL3: D203.1 (K), D213.1 (K), D223.1 (K), D233.1 (K), D243.1 (K), D253.1 (K), D263.1 (K), D273.1 (K), R33.1; also elsewhere on the board
COL4: D204.1 (K), D214.1 (K), D224.1 (K), D234.1 (K), D244.1 (K), D254.1 (K), D264.1 (K), D274.1 (K), R34.1; also elsewhere on the board
COL5: D205.1 (K), D215.1 (K), D225.1 (K), D235.1 (K), D245.1 (K), D255.1 (K), D265.1 (K), D275.1 (K), R35.1; also elsewhere on the board
COL6: D206.1 (K), D216.1 (K), D226.1 (K), D236.1 (K), D246.1 (K), D256.1 (K), D266.1 (K), D276.1 (K), R36.1; also elsewhere on the board
DIFF: U14.6 (E3); also elsewhere on the board
GND: R30.2, R31.2, R32.2, R33.2, R34.2, R35.2, R36.2, U14.4 (~E1), U14.5 (~E2), U14.8 (GND); also elsewhere on the board
ROW0: D200.2 (A), D201.2 (A), D202.2 (A), D203.2 (A), D204.2 (A), D205.2 (A), D206.2 (A), U14.15 (Y0)
ROW1: D210.2 (A), D211.2 (A), D212.2 (A), D213.2 (A), D214.2 (A), D215.2 (A), D216.2 (A), U14.14 (Y1)
ROW2: D220.2 (A), D221.2 (A), D222.2 (A), D223.2 (A), D224.2 (A), D225.2 (A), D226.2 (A), U14.13 (Y2)
ROW3: D230.2 (A), D231.2 (A), D232.2 (A), D233.2 (A), D234.2 (A), D235.2 (A), D236.2 (A), U14.12 (Y3)
ROW4: D240.2 (A), D241.2 (A), D242.2 (A), D243.2 (A), D244.2 (A), D245.2 (A), D246.2 (A), U14.11 (Y4)
ROW5: D250.2 (A), D251.2 (A), D252.2 (A), D253.2 (A), D254.2 (A), D255.2 (A), D256.2 (A), U14.10 (Y5)
ROW6: D260.2 (A), D261.2 (A), D262.2 (A), D263.2 (A), D264.2 (A), D265.2 (A), D266.2 (A), U14.9 (Y6)
ROW7: D270.2 (A), D271.2 (A), D272.2 (A), D273.2 (A), D274.2 (A), D275.2 (A), D276.2 (A), U14.7 (Y7)

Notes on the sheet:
DEFAULT MAP - fit the diodes marked "1" (27 of 56): key code char b6 b5 b4 b3 b2 b1 b0 K1 0x0D CR Enter 0 0 0 1 1 0 1 K2 0x09 HT Tab 0 0 0 1 0 0 1 K3 0x1B ESC 0 0 1 1 0 1 1 K4 0x03 ETX Ctrl-C 0 0 0 0 0 1 1 K5 0x2F '/' 0 1 0 1 1 1 1 K6 0x3F '?' 0 1 1 1 1 1 1 K7 0x20 SP Space 0 1 0 0 0 0 0 K8 0x71 'q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
'238, not '138: the outputs must go HIGH to push current through the diodes into the pull-downs. A 74HC138 has active-LOW outputs and would need pull-ups and the opposite diode orientation. E2 = DIFF, so the ROM is powered only while a key change is pending. DIFF asserts within ~60 ns of the scan s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
Cathode -> column, anode -> row. Unselected rows sit at 0 V, so their diodes are reverse biased: no sneak paths. A selected column sits one 1N4148 drop below the 3.3 V row: about 2.76 V (0.54 V at 184 uA into 15k) against the 2.31 V VIH of the 74HC165 - 450 mV of margin. 10k works as well (2.74 V);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
ASCII DIODE ROM - 8 rows x 7 bits
